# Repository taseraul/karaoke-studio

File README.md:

# karaoke-studio
Mic preamp + bluetooth in +  line in

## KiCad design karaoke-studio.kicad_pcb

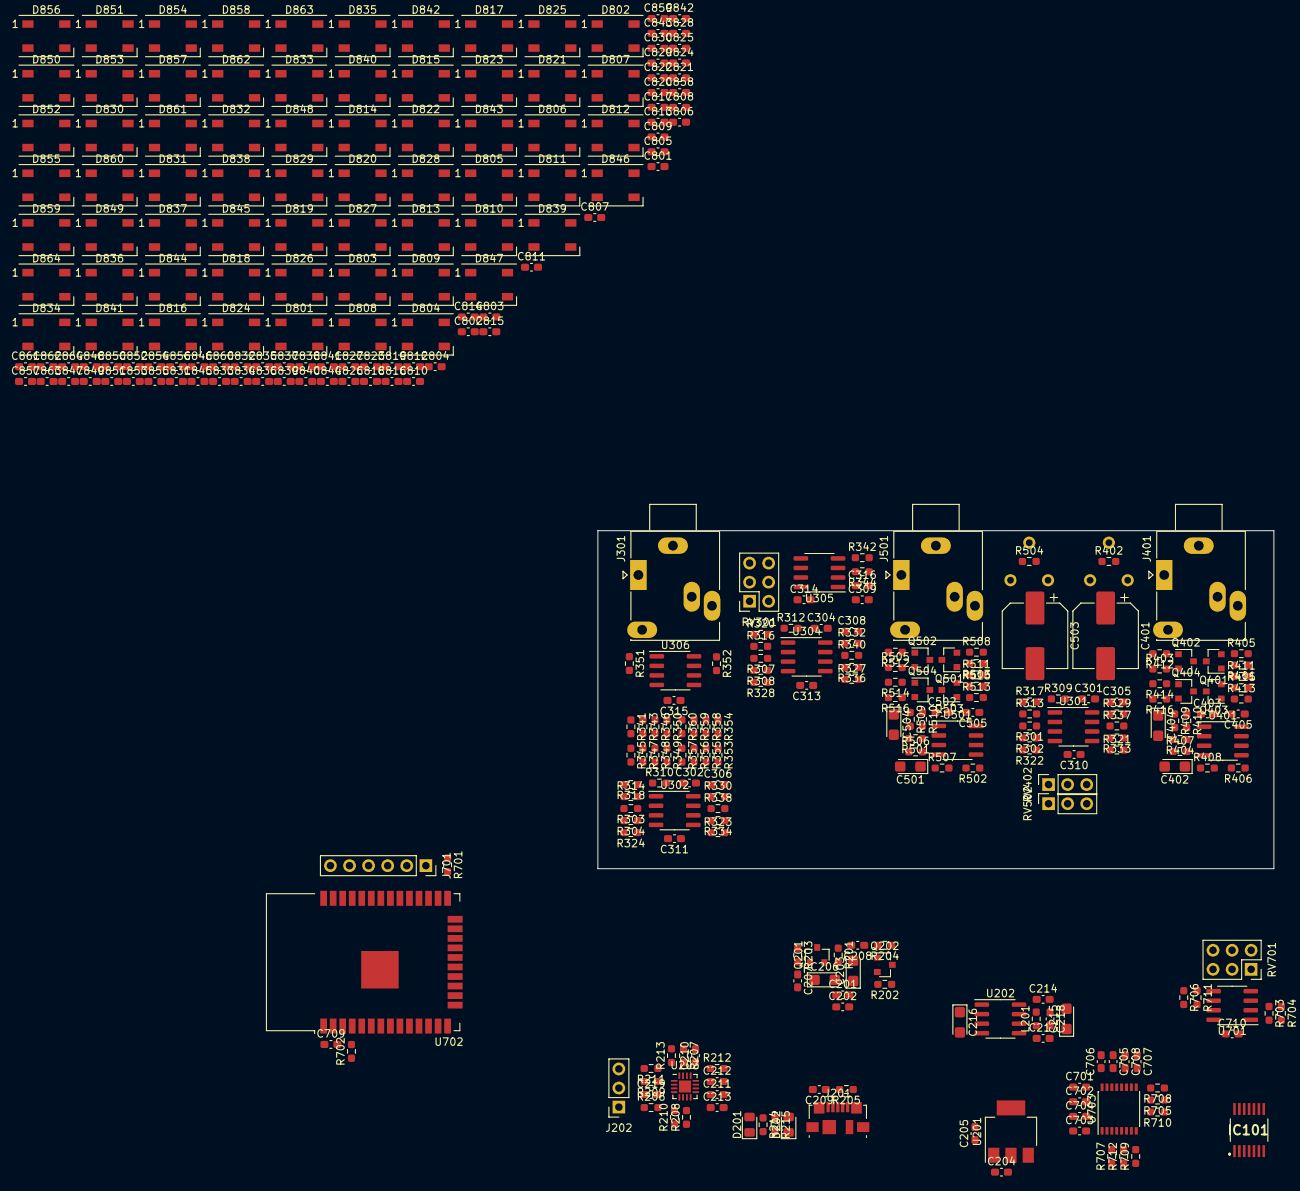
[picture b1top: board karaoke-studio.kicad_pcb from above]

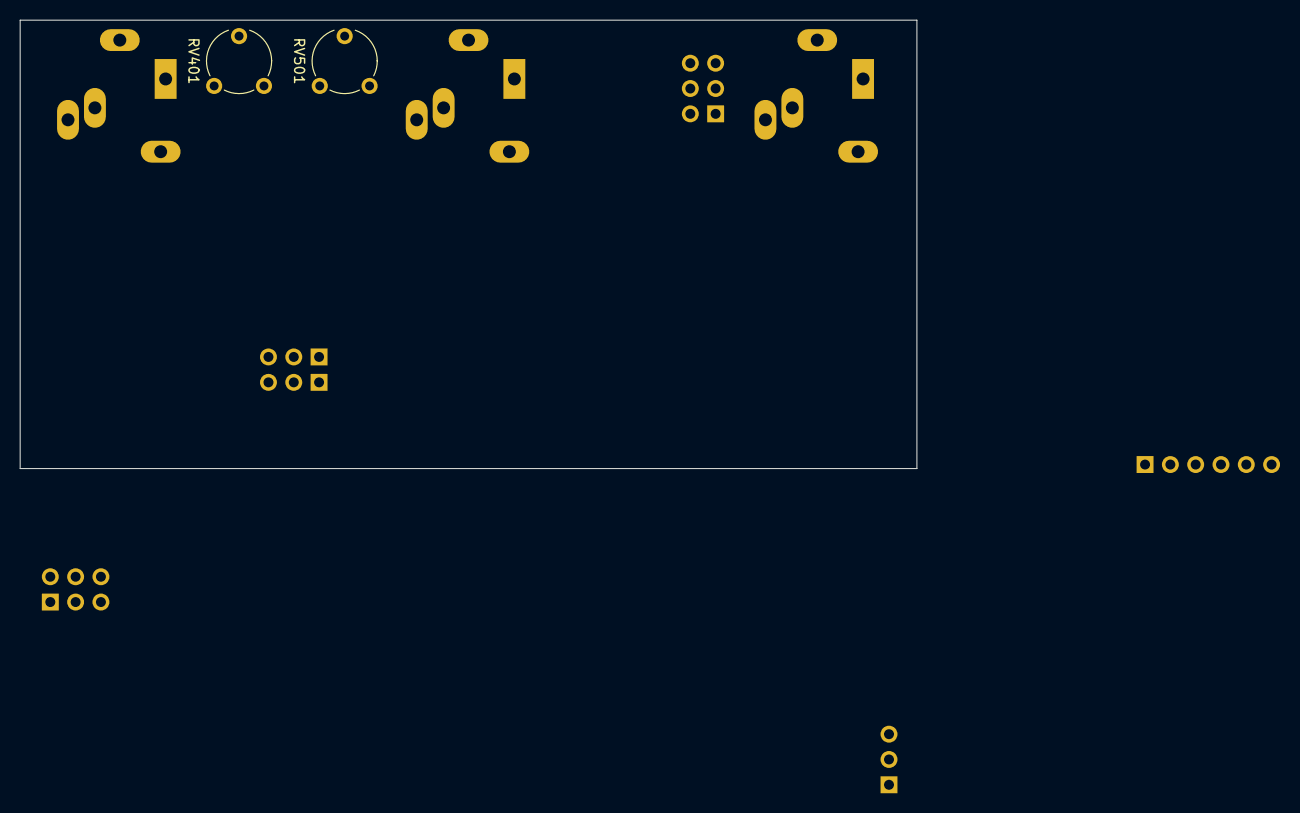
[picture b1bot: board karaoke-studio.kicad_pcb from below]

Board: 2 copper layers, 90.0 x 45.0 mm, 328 parts (2 on the bottom side), 188 nets, no tracks yet.

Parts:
C201, C213: 100n; C_0603_1608Metric_Pad1.08x0.95mm_HandSolder
C202, C204, C205, C207, C208, C209, C210, C211, C214, C219, C309, C310, C311, C313, C314, C315, C316, C405, C505, C701, C704, C705, C706, C708, C709, C710: 10u; C_0603_1608Metric_Pad1.08x0.95mm_HandSolder
C203, C206, C215, C216, C402, C404, C501, C504: 10u; CP_EIA-3216-10_Kemet-I
C212, C403, C502, C801, C802, C803, C804, C805, C806, C807, C808, C809, C810, C811, C812, C813, C814, C815, C816, C817, C818, C819, C820, C821, C822, C823, C824, C825, C826, C827, C828, C829, C830, C831, C832, C833, C834, C835, C836, C837, C838, C839, C840, C841, C842, C843, C844, C845, C846, C847, C848, C849, C850, C851, C852, C853, C854, C855, C856, C857, C858, C859, C860, C861, C862, C863, C864: 1u; C_0603_1608Metric_Pad1.08x0.95mm_HandSolder
C217, C218: NC; C_0603_1608Metric_Pad1.08x0.95mm_HandSolder
C301, C302, C304, C305, C306, C308: 10n; C_0603_1608Metric_Pad1.08x0.95mm_HandSolder
C401, C503: 1000u; CP_Elec_8x10.5
C702, C703, C707: 0.1u; C_0603_1608Metric_Pad1.08x0.95mm_HandSolder
D201, D202: LED; LED_0805_2012Metric_Pad1.15x1.40mm_HandSolder
D801, D802, D803, D804, D805, D806, D807, D808, D809, D810, D811, D812, D813, D814, D815, D816, D817, D818, D819, D820, D821, D822, D823, D824, D825, D826, D827, D828, D829, D830, D831, D832, D833, D834, D835, D836, D837, D838, D839, D840, D841, D842, D843, D844, D845, D846, D847, D848, D849, D850, D851, D852, D853, D854, D855, D856, D857, D858, D859, D860, D861, D862, D863, D864: WS2812B; LED_WS2812B_PLCC4_5.0x5.0mm_P3.2mm
IC101: PCM1807PWR; PCM1808PWR
J201: USB_B_Mini; USB_Micro-B_Molex_47346-0001
J202: Conn_01x03; PinSocket_1x03_P2.54mm_Vertical
J301, J401, J501: AudioJack3; Jack_3.5mm_Ledino_KB3SPRS_Horizontal
J701: Conn_01x06; PinSocket_1x06_P2.54mm_Vertical
L201: 0; R_0603_1608Metric_Pad0.98x0.95mm_HandSolder
Q201, Q401, Q402, Q501, Q502: MMBT4403; SOT-23
Q202, Q403, Q404, Q503, Q504: BC849; SOT-23
R201, R202, R205, R206, R207, R208, R210, R345, R347, R348, R349, R353, R355, R356, R357: 0; R_0603_1608Metric_Pad0.98x0.95mm_HandSolder
R203, R204: 47k; R_0603_1608Metric_Pad0.98x0.95mm_HandSolder
R209, R211, R342, R344, R701, R702, R705, R707, R708, R709, R710, R712: 10k; R_0603_1608Metric_Pad0.98x0.95mm_HandSolder
R212: 1.2k; R_0603_1608Metric_Pad0.98x0.95mm_HandSolder
R213, R309, R310, R312, R329, R330, R332: 1k; R_0603_1608Metric_Pad0.98x0.95mm_HandSolder
R214, R215: 2k; R_0603_1608Metric_Pad0.98x0.95mm_HandSolder
R301, R303, R307, R313, R314, R316, R321, R323, R327, R333, R334, R336, R402, R404, R406, R410, R501, R502, R504, R510: 100k; R_0603_1608Metric_Pad0.98x0.95mm_HandSolder
R302, R304, R308, R317, R318, R320, R322, R324, R328, R337, R338, R340: 33k; R_0603_1608Metric_Pad0.98x0.95mm_HandSolder
R341, R343, R346, R350, R354, R358, R359, R360, R703, R711: 5.1k; R_0603_1608Metric_Pad0.98x0.95mm_HandSolder
R351, R352: 100; R_0603_1608Metric_Pad0.98x0.95mm_HandSolder
R401, R403, R503, R505: 4.7k; R_0603_1608Metric_Pad0.98x0.95mm_HandSolder
R405, R508: 22; R_0603_1608Metric_Pad0.98x0.95mm_HandSolder
R407, R409, R506, R509: 22k; R_0603_1608Metric_Pad0.98x0.95mm_HandSolder
R408, R411, R412, R507, R511, R512: 3.3k; R_0603_1608Metric_Pad0.98x0.95mm_HandSolder
R413, R414, R513, R514: 680; R_0603_1608Metric_Pad0.98x0.95mm_HandSolder
R415, R416, R515, R516: 2.2k; R_0603_1608Metric_Pad0.98x0.95mm_HandSolder
R704, R706: 200k; R_0603_1608Metric_Pad0.98x0.95mm_HandSolder
RV301, RV701: R_POT_Dual_Separate; PinSocket_2x03_P2.54mm_Vertical
RV401, RV501: 10k; Potentiometer_Piher_PT-6-V_Vertical
RV402, RV502: 10k; PinSocket_1x03_P2.54mm_Vertical
U201: AP1117-33; SOT-223-3_TabPin2
U202: ICL7660; SOIC-8_3.9x4.9mm_P1.27mm
U203: BQ24074RGT; VQFN-16-1EP_3x3mm_P0.5mm_EP1.6x1.6mm
U301, U302, U304, U305, U306, U401, U501, U701: NE5532; SOIC-8_3.9x4.9mm_P1.27mm
U702: ESP32-WROOM-32
U703: UDA1334ATS; SSOP-16_4.4x5.2mm_P0.65mm

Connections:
+3V3: C205.2, C701.2, C702.2, C703.2, C704.2, C709.2, J701.1, R342.2, R701.1, R702.1, U201.2, U702.2, U703.4, U703.13
+5VA: C201.2, C202.2, C203.1, C310.1, C311.1, C313.1, C314.1, C315.1, C405.1, C505.1, C710.1, Q202.2, R202.2, R401.1, R403.1, R503.1, R505.1, U301.8, U302.8, U304.8, U305.8, U306.8, U401.8, U501.8, U701.8
+BATT: C204.2, C211.1, C212.1, C213.1, C214.1, C801.1, C802.1, C803.1, C804.1, C805.1, C806.1, C807.1, C808.1, C809.1, C810.1, C811.1, C812.1, C813.1, C814.1, C815.1, C816.1, C817.1, C818.1, C819.1, C820.1, C821.1, C822.1, C823.1, C824.1, C825.1, C826.1, C827.1, C828.1, C829.1, C830.1, C831.1, C832.1, C833.1, C834.1, C835.1, C836.1, C837.1, C838.1, C839.1, C840.1, C841.1, C842.1, C843.1, C844.1, C845.1, C846.1, C847.1, C848.1, C849.1, C850.1, C851.1, C852.1, C853.1, C854.1, C855.1, C856.1, C857.1, C858.1, C859.1, C860.1, C861.1, C862.1, C863.1, C864.1, D801.1, D802.1, D803.1, D804.1, D805.1, D806.1, D807.1, D808.1, D809.1, D810.1, D811.1, D812.1, D813.1, D814.1, D815.1, D816.1, D817.1, D818.1, D819.1, D820.1, D821.1, D822.1, D823.1, D824.1, D825.1, D826.1, D827.1, D828.1, D829.1, D830.1, D831.1, D832.1, D833.1, D834.1, D835.1, D836.1, D837.1, D838.1, D839.1, D840.1, D841.1, D842.1, D843.1, D844.1, D845.1, D846.1, D847.1, D848.1, D849.1, D850.1, D851.1, D852.1, D853.1, D854.1, D855.1, D856.1, D857.1, D858.1, D859.1, D860.1, D861.1, D862.1, D863.1, D864.1, Q202.3, R202.1, R204.1, R214.1, R215.1, U201.3, U202.8, U203.10, U203.11
-5VA: C201.1, C202.1, C206.2, C310.2, C311.2, C313.2, C314.2, C315.2, C405.2, C505.2, C710.2, Q201.2, R201.2, R415.2, R416.2, R515.2, R516.2, U301.4, U302.4, U304.4, U305.4, U306.4, U401.4, U501.4, U701.4
-BATT: C215.2, C218.1, L201.2, Q201.3, R201.1, R203.1
ADC1_4: C306.1, R330.2, U702.8
ADC1_5: C302.1, R310.2, U702.9
ADC1_6: C305.1, R329.2, U702.6
ADC1_7: C301.1, R309.2, U702.7
ADC2_4: C304.1, R312.2, U702.16
ADC2_6: C308.1, R332.2, U702.13
BCK: U702.11, U703.1
BOOT: J701.5, R701.2, U702.25
BT_OUT_L: R303.2, R345.2, RV701.2, U701.1
BT_OUT_R: R323.2, R357.2, RV701.5, U701.7
DATA: U702.36, U703.3
EN: J701.2, R702.2, U702.3
GND: C203.2, C204.1, C205.1, C206.1, C207.2, C208.2, C209.2, C210.2, C211.2, C212.2, C213.2, C214.2, C215.1, C217.2, C218.2, C219.1, C301.2, C302.2, C304.2, C305.2, C306.2, C308.2, C309.2, C316.2, C701.1, C702.1, C703.1, C704.1, C707.1, C708.1, C709.1, C801.2, C802.2, C803.2, C804.2, C805.2, C806.2, C807.2, C808.2, C809.2, C810.2, C811.2, C812.2, C813.2, C814.2, C815.2, C816.2, C817.2, C818.2, C819.2, C820.2, C821.2, C822.2, C823.2, C824.2, C825.2, C826.2, C827.2, C828.2, C829.2, C830.2, C831.2, C832.2, C833.2, C834.2, C835.2, C836.2, C837.2, C838.2, C839.2, C840.2, C841.2, C842.2, C843.2, C844.2, C845.2, C846.2, C847.2, C848.2, C849.2, C850.2, C851.2, C852.2, C853.2, C854.2, C855.2, C856.2, C857.2, C858.2, C859.2, C860.2, C861.2, C862.2, C863.2, C864.2, D801.3, D802.3, D803.3, D804.3, D805.3, D806.3, D807.3, D808.3, D809.3, D810.3, D811.3, D812.3, D813.3, D814.3, D815.3, D816.3, D817.3, D818.3, D819.3, D820.3, D821.3, D822.3, D823.3, D824.3, D825.3, D826.3, D827.3, D828.3, D829.3, D830.3, D831.3, D832.3, D833.3, D834.3, D835.3, D836.3, D837.3, D838.3, D839.3, D840.3, D841.3, D842.3, D843.3, D844.3, D845.3, D846.3, D847.3, D848.3, D849.3, D850.3, D851.3, D852.3, D853.3, D854.3, D855.3, D856.3, D857.3, D858.3, D859.3, D860.3, D861.3, D862.3, D863.3, D864.3, J201.5, J201.6, J202.3, J301.S, J401.S, J501.S, J701.6, R206.1, R207.1, R208.1, R210.1, R211.2, R212.2, R213.2, R313.1, R314.1, R316.1, R333.1, R334.1, R336.1, R344.1, R404.2, R406.1, R411.2, R412.2, R501.2, R502.1, R511.2, R512.2, R704.1, R705.1, R706.1, R707.1, R708.1, R709.1, R710.1, R712.1, U201.1, U202.3, U203.8, U203.17, U306.3, U306.5, U401.5, U501.5, U701.3, U701.5, U702.1, U702.15, U702.38, U702.39, U703.5, U703.15
IN1+: C404.2, Q404.2, R414.2, R416.1
IN1-: C402.2, Q403.2, R413.2, R415.1
IN2+: C504.2, Q504.2, R514.2, R516.1
IN2-: C501.2, Q503.2, R513.2, R515.1
LED: D801.4, U702.26
MASTER_L: R307.2, R351.2, RV301.2, U306.1
MASTER_R: R327.2, R352.2, RV301.5, U306.7
MIC1_AMP_OUT: R321.2, R348.2, R355.2, RV402.2, U401.7
MIC1_IN+: J401.T, Q402.1, R412.1
MIC1_IN-: J401.R, Q401.1, R411.1
MIC2_AMP_OUT: R301.2, R349.2, R353.2, RV502.2, U501.7
MIC2_IN+: J501.T, Q502.1, R512.1
MIC2_IN-: J501.R, Q501.1, R511.1
unnamed: C207.1, Q201.1, R203.2
unnamed: C208.1, Q202.1, R204.2
unnamed: C216.1, U202.2
unnamed: C216.2, U202.4
unnamed: C217.1, L201.1, U202.5
unnamed: C219.2, J202.1, R209.1, U203.2, U203.3
unnamed: C401.1, R402.2, RV401.3
unnamed: C401.2, Q402.3, Q404.3, R403.2
unnamed: C402.1, R407.1
unnamed: C403.1, R410.1, U401.1
unnamed: C403.2, R406.2, R408.2
unnamed: C404.1, R409.1
unnamed: C501.1, R506.1
unnamed: C502.1, R510.1, U501.1
unnamed: C502.2, R502.2, R507.2
unnamed: C503.1, R504.2, RV501.3
unnamed: C503.2, Q502.3, Q504.3, R505.2
unnamed: C504.1, R509.1
unnamed: C705.1, R703.2, R704.2
unnamed: C705.2, U703.14
unnamed: C706.1, U703.16
unnamed: C706.2, R706.2, R711.2
unnamed: C707.2, C708.2, U703.12
unnamed: D201.1, R214.2
unnamed: D201.2, U203.7
unnamed: D202.1, R215.2
unnamed: D202.2, U203.9
unnamed: D801.2, D802.4
unnamed: D802.2, D803.4
unnamed: D803.2, D804.4
unnamed: D804.2, D805.4
unnamed: D805.2, D806.4
unnamed: D806.2, D807.4
unnamed: D807.2, D808.4
unnamed: D808.2, D809.4
unnamed: D809.2, D810.4
unnamed: D810.2, D820.4
unnamed: D811.2, D821.4
unnamed: D811.4, D812.2
unnamed: D812.4, D813.2
unnamed: D813.4, D814.2
unnamed: D814.4, D815.2
unnamed: D815.4, D816.2
unnamed: D816.4, D817.2
unnamed: D817.4, D818.2
unnamed: D818.4, D819.2
unnamed: D819.4, D820.2
unnamed: D821.2, D822.4
unnamed: D822.2, D823.4
unnamed: D823.2, D824.4
unnamed: D824.2, D825.4
unnamed: D825.2, D826.4
unnamed: D826.2, D827.4
unnamed: D827.2, D828.4
unnamed: D828.2, D829.4
unnamed: D829.2, D830.4
unnamed: D830.2, D840.4
unnamed: D831.2, D841.4
unnamed: D831.4, D832.2
unnamed: D832.4, D833.2
unnamed: D833.4, D834.2
unnamed: D834.4, D835.2
unnamed: D835.4, D836.2
unnamed: D836.4, D837.2
unnamed: D837.4, D838.2
unnamed: D838.4, D839.2
unnamed: D839.4, D840.2
unnamed: D841.2, D842.4
unnamed: D842.2, D843.4
unnamed: D843.2, D844.4
unnamed: D844.2, D845.4
unnamed: D845.2, D846.4
unnamed: D846.2, D847.4
unnamed: D847.2, D848.4
unnamed: D848.2, D849.4
unnamed: D849.2, D850.4
unnamed: D850.2, D860.4
unnamed: D851.2, D861.4
unnamed: D851.4, D852.2
unnamed: D852.4, D853.2
unnamed: D853.4, D854.2
unnamed: D854.4, D855.2
unnamed: D855.4, D856.2
unnamed: D856.4, D857.2
unnamed: D857.4, D858.2
unnamed: D858.4, D859.2
unnamed: D859.4, D860.2
unnamed: D861.2, D862.4
unnamed: D862.2, D863.4
unnamed: D863.2, D864.4
unnamed: J201.2, R205.2
unnamed: J201.3, R205.1
unnamed: J202.2, R209.2, R211.1, U203.1
unnamed: J301.R, R352.1
unnamed: J301.T, R351.1
unnamed: Q401.2, Q403.1, R413.1
unnamed: Q401.3, Q403.3, R401.2, R405.1
unnamed: Q402.2, Q404.1, R414.1
unnamed: Q501.2, Q503.1, R513.1
unnamed: Q501.3, Q503.3, R503.2, R508.1
unnamed: Q502.2, Q504.1, R514.1
unnamed: R206.2, U203.4
unnamed: R207.2, U203.14
unnamed: R208.2, U203.6
unnamed: R210.2, U203.5
unnamed: R212.1, U203.12
unnamed: R213.1, U203.16
unnamed: R301.1, R302.1, U301.3
unnamed: R303.1, R304.1, U302.3
unnamed: R307.1, R308.1, U304.3
unnamed: R309.1, R317.2, U301.1
unnamed: R310.1, R318.2, U302.1
unnamed: R312.1, R320.2, U304.1
unnamed: R313.2, R317.1, U301.2
unnamed: R314.2, R318.1, U302.2
unnamed: R316.2, R320.1, U304.2
unnamed: R321.1, R322.1, U301.5
unnamed: R323.1, R324.1, U302.5
unnamed: R327.1, R328.1, U304.5
unnamed: R329.1, R337.2, U301.7
unnamed: R330.1, R338.2, U302.7
unnamed: R332.1, R340.2, U304.7
unnamed: R333.2, R337.1, U301.6
unnamed: R334.2, R338.1, U302.6
unnamed: R336.2, R340.1, U304.6
unnamed: R341.1, R343.1, R346.1, R350.1, RV301.1, U306.2
unnamed: R341.2, R345.1
unnamed: R342.1, R344.2, U305.3, U305.5
unnamed: R343.2, R347.1
unnamed: R346.2, R348.1
unnamed: R349.1, R350.2
unnamed: R353.1, R354.2
unnamed: R354.1, R358.1, R359.1, R360.1, RV301.6, U306.6
unnamed: R355.1, R358.2
unnamed: R356.1, R359.2
unnamed: R357.1, R360.2
unnamed: R402.1, R405.2, RV401.1, RV401.2
unnamed: R404.1, R407.2, U401.3
unnamed: R408.1, RV402.1, U401.6
unnamed: R409.2, R410.2, U401.2
unnamed: R501.1, R506.2, U501.3
unnamed: R504.1, R508.2, RV501.1, RV501.2
unnamed: R507.1, RV502.1, U501.6
unnamed: R509.2, R510.2, U501.2
unnamed: R703.1, RV701.3, U701.2
unnamed: R705.2, U703.10
unnamed: R707.2, U703.6
unnamed: R708.2, U703.9
unnamed: R709.2, U703.8
unnamed: R710.2, U703.11
unnamed: R711.1, RV701.4, U701.6
unnamed: R712.2, U703.7
RX: J701.3, U702.34
TX: J701.4, U702.35
VCC: C209.1, C210.1, J201.1, U203.13
V_REF: C309.1, C316.1, R302.2, R304.2, R308.2, R322.2, R324.2, R328.2, U305.1, U305.2, U305.6, U305.7
WS: U702.10, U703.2

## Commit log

2021-06-11 Almost finshed schematic, started layout
